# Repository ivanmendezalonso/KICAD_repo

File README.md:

# KICAD_repo
 Aqui estaran todos las carpetas de proyectos

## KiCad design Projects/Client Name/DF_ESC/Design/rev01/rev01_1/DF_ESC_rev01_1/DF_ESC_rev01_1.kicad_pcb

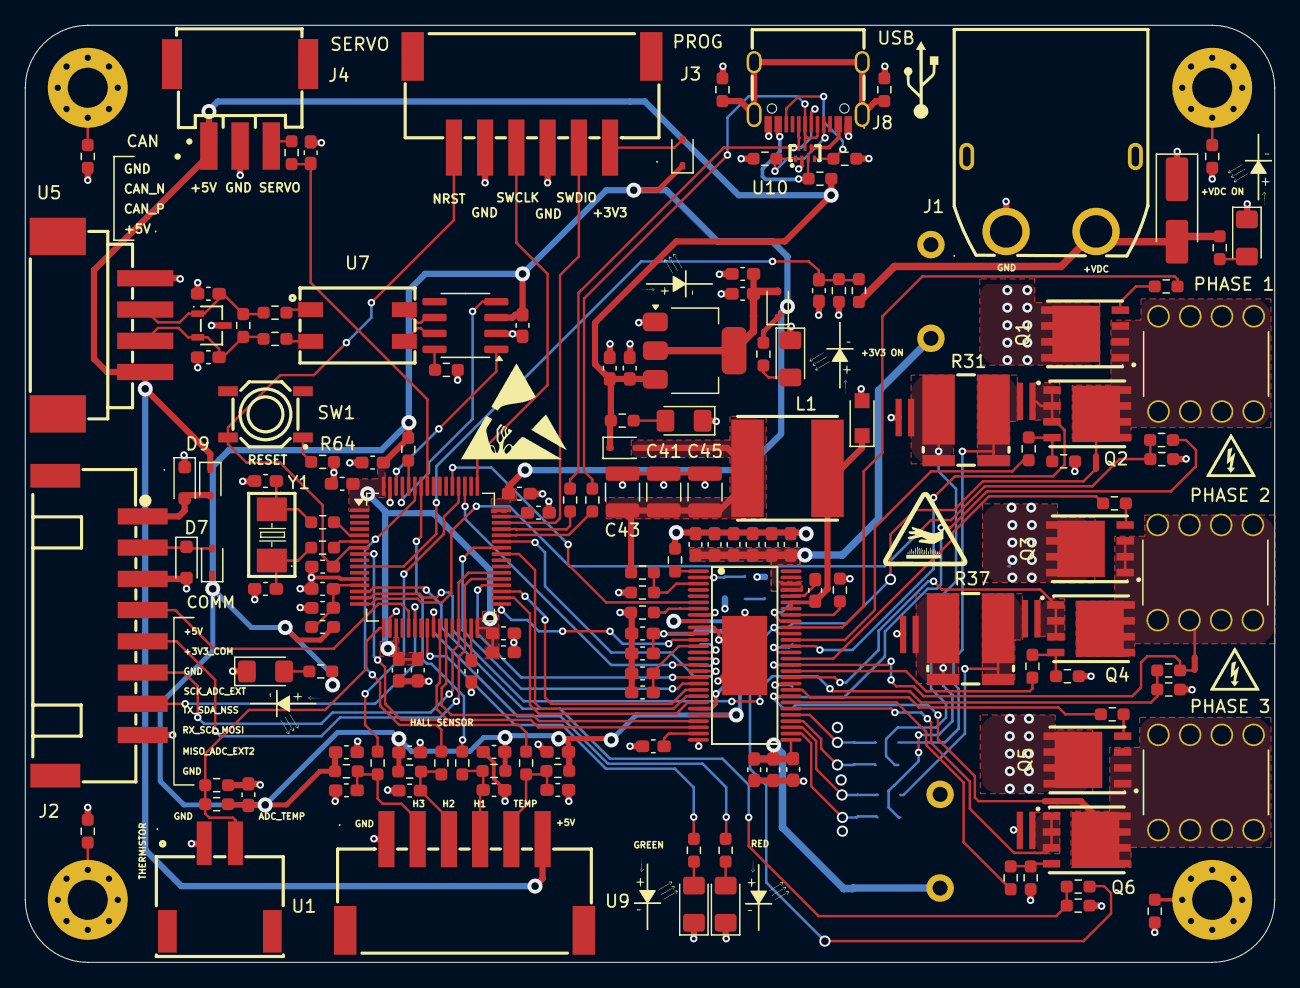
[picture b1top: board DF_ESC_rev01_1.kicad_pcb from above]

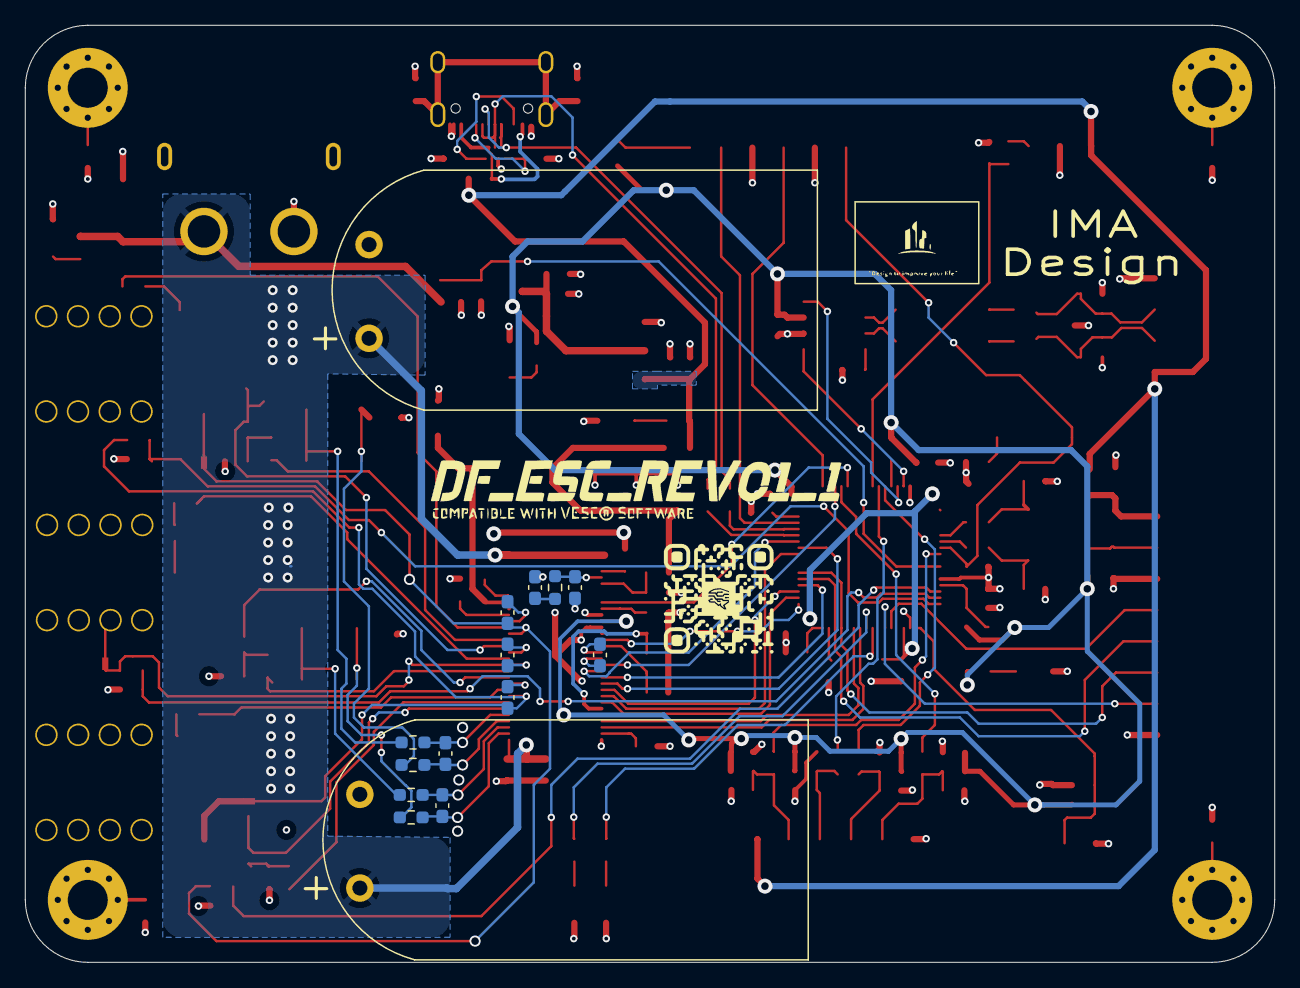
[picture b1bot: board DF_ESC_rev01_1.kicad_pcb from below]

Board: 4 copper layers, 100.0 x 75.0 mm, 183 parts (18 on the bottom side), 125 nets.

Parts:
C1, C2: LKMI2501K821MF; CAP-TH_BD18.0-P7.50-D1.2-SIDE
C3, C4, C10, C11, C12, C15, C16, C17, C19, C21, C23, C32, C33, C34, C35, C39, C42, C46, C57, C58, C59, C60: 100n; C_0603_1608Metric_Pad1.08x0.95mm_HandSolder
C5, C6, C7, C8, C22, C36, C37, C38, C40, C44, C47: 1u; C_0603_1608Metric_Pad1.08x0.95mm_HandSolder
C9: 10u; C_0603_1608Metric_Pad1.08x0.95mm_HandSolder
C13, C14: C; C_0603_1608Metric_Pad1.08x0.95mm_HandSolder
C18, C20, C24, C25, C27, C28, C31: 2u2; C_0603_1608Metric_Pad1.08x0.95mm_HandSolder
C26: 10n; C_0603_1608Metric_Pad1.08x0.95mm_HandSolder
C29: 120p; C_0603_1608Metric_Pad1.08x0.95mm_HandSolder
C30: 22n; C_0603_1608Metric_Pad1.08x0.95mm_HandSolder
C41, C43, C45: 10u; C_1210_3225Metric
C48, C49: 2n2; C_0603_1608Metric_Pad1.08x0.95mm_HandSolder
C50, C51, C52: 51p; C_0603_1608Metric_Pad1.08x0.95mm_HandSolder
C53, C54, C55, C56: 4n7; C_0603_1608Metric_Pad1.08x0.95mm_HandSolder
D1: SMAJ60CA; D_SMA_Handsoldering
D2, D3, D5, D11: LED_G; LED_1206_3216Metric_Pad1.42x1.75mm_HandSolder
D4, D8, D10, D13, D15: BAT60A; D_SOD-323
D6: LED; LED_1206_3216Metric_Pad1.42x1.75mm_HandSolder
D7: PESD3V3U1UA,115; D_SOD-323_HandSoldering
D9: SD05_SOD323; D_SOD-323_HandSoldering
D12: LED_R; LED_1206_3216Metric_Pad1.42x1.75mm_HandSolder
D14: PMEG6020AELR; Nexperia_CFP3_SOD-123W
FB1: FerriteBead; L_0603_1608Metric_Pad1.05x0.95mm_HandSolder
H1, H2, H3, H4: MountingHole_Pad; MountingHole_3.2mm_M3_Pad_Via
J1: XT60PW-M; CONN-TH_XT60PW-M
J2: HX25003-8AWB; CONN-SMD_8P-P2.50_HX25003-8AWB
J3: S6B-XH-SM4-TB(LF)(SN); CONN-SMD_S6B-XH-SM4-TB-LF-SN
J4: XH-3AWB; CONN-SMD_XH-3AWB
J5, J6, J7: 7461084; WE_7461084
J8: USB_C_Receptacle_USB2.0; USB-C_SMD-TYPE-C-31-M-12
L1: 22u; IND-SMD_L7.8-W7.8_SDR0805
LOGO1: DF_LOGO; DF_ESC_REV01_1_LOGO
LOGO2: DF_LOGO_NO_SLK
NT1, NT4, NT7: NetTie_2; NetTie-2_SMD_Pad0.5mm
NT2, NT3, NT5, NT6, NT8: Net_Tie_PWR; NetTie_SMD_Pad_3.00mm
Q1, Q2, Q3, Q4, Q5, Q6: HSBA15810C; PQFN-8_L6.0-W5.0-P1.27-LS6.0-BL
QR1: DF_QR_CODE
R1, R3, R13, R21, R23, R25, R45, R46, R47, R48, R64: 2k2; R_0603_1608Metric_Pad0.98x0.95mm_HandSolder
R2, R4, R30, R36, R40: 39k; R_0603_1608Metric_Pad0.98x0.95mm_HandSolder
R5, R6, R7, R10, R11: 1k; R_0603_1608Metric_Pad0.98x0.95mm_HandSolder
R8, R9: R; R_0603_1608Metric_Pad0.98x0.95mm_HandSolder
R12, R53, R54, R55, R60, R61, R62, R63: 0R; R_0603_1608Metric_Pad0.98x0.95mm_HandSolder
R14: 16k; R_0603_1608Metric_Pad0.98x0.95mm_HandSolder
R15, R49, R50, R51, R52: 10k; R_0603_1608Metric_Pad0.98x0.95mm_HandSolder
R16: 205k; R_0603_1608Metric_Pad0.98x0.95mm_HandSolder
R17: 1M; R_0603_1608Metric_Pad0.98x0.95mm_HandSolder
R18, R20, R22, R24: 18k; R_0603_1608Metric_Pad0.98x0.95mm_HandSolder
R19: 3k3; R_0603_1608Metric_Pad0.98x0.95mm_HandSolder
R26, R27, R32, R33, R38, R39: 4R7; R_0603_1608Metric_Pad0.98x0.95mm_HandSolder
R28, R29, R34, R35: 100R; R_0603_1608Metric_Pad0.98x0.95mm_HandSolder
R31, R37: 0R001; RES-SMD_L7.0-W6.7
R41: 120R; R_0603_1608Metric_Pad0.98x0.95mm_HandSolder
R42, R43, R44: 10R; R_0603_1608Metric_Pad0.98x0.95mm_HandSolder
R56, R57: 5k1; R_0603_1608Metric_Pad0.98x0.95mm_HandSolder
R58, R59: 22R; R_0603_1608Metric_Pad0.98x0.95mm_HandSolder
SW1: SW_DIP_x01; SW-SMD_4P-L5.2-W5.2-P3.70-LS6.4
TH1: Thermistor_NTC; R_0603_1608Metric_Pad0.98x0.95mm_HandSolder
U1: XH-2PWBPZ; CONN-SMD_XH-2PWBPZ
U2: AMS1117-3.3; SOT-223-3_TabPin2
U3: STM32F405RGTx; LQFP-64_10x10mm_P0.5mm
U4: DRV8302DCAR; HTSSOP-56_L14.0-W6.1-P0.50-LS8.1-BL-EP
U5: S4B-XH-SM4-TB-(LF)(SN); CONN-SMD_S4B-XH-SM4-TB-LF-SN
U6: ESDCAN24-2BLY; SOT-23-3_L3.0-W1.7-P0.95-LS2.9-BR
U7: 744227S; FILTER-SMD_4P-L9.2-W6.0-P2.54-TL
U8: SN65HVD230; SOIC-8_3.9x4.9mm_P1.27mm
U9: S6B-XH-SM4-TB(LF)(SN); CONN-SMD_S6B-XH-SM4-TB-LF-SN
U10: PUSB3AB6Z; XSON-7_L2.2-W1.2-P0.50-BL
Y1: Crystal_Small; CRYSTAL-SMD_L5.0-W3.2

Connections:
+3V3: C3.1, C9.1, C10.1, C11.1, C12.1, C15.1, C16.1, C17.1, C52.1, C57.1, C58.1, C59.1, C60.1, D4.1 (K), D8.1 (K), D13.1 (K), FB1.2, R1.1, R6.1, R7.1, R12.1, R45.1, R46.1, R47.1, R48.1, U3.1 (VBAT), U3.19 (VDD), U3.32 (VDD), U3.48 (VDD), U3.64 (VDD), U4.9 (M_OC), U4.24 (REF), U8.3 (VCC)
+5V: C5.1, C6.1, D10.1 (K), D15.1 (K), J4.1, R5.1, R55.1, U2.3 (VI), U5.4, U9.6
+VDC: C1.1, C2.1, C32.2, C33.2, C35.2, C36.1, C37.1, C38.1, C40.1, C44.1, C47.1, D1.2 (A2), J1.2 (+), Q1.5 (D), Q1.6 (D), Q1.7 (D), Q1.8 (D), Q1.9 (D), Q3.5 (D), Q3.6 (D), Q3.7 (D), Q3.8 (D), Q3.9 (D), Q5.5 (D), Q5.6 (D), Q5.7 (D), Q5.8 (D), Q5.9 (D), R2.1, R4.1, U4.29 (PVDD1), U4.53 (PVDD2), U4.54 (PVDD2)
/[3] - STEP DOWN/+3V3_IC: C7.1, C8.1, D4.2 (A), U2.2 (VO)
/[4] - MCU/+3V3_COM: D7.1, D8.2 (A), J2.2
/[4] - MCU/+5V_COM: D9.2 (A2), D10.2 (A), J2.1
/[4] - MCU/BOOT0_P: R12.2, U3.60 (BOOT0)
/[4] - MCU/LED_GREEN: R10.1, U3.24 (PC4)
/[4] - MCU/LED_RED: R11.1, U3.25 (PC5)
/[4] - MCU/MISO_ADC_EXT2: J2.7, U3.22 (PA6)
/[4] - MCU/NRST: C19.1, J3.6, SW1.2, U3.7 (NRST)
/[4] - MCU/PH_0: C13.2, R8.1, Y1.2
/[4] - MCU/PH_0_P: R8.2, U3.5 (PH0)
/[4] - MCU/PH_1: C14.2, R9.1, Y1.1
/[4] - MCU/PH_1_P: R9.2, U3.6 (PH1)
/[4] - MCU/RX_SCL_MOSI: J2.6, U3.29 (PB10), U3.38 (PC7)
/[4] - MCU/SCK_ADC_EXT: J2.4, U3.21 (PA5)
/[4] - MCU/SERVO: C23.1, R13.1, U3.57 (PB5)
/[4] - MCU/SWCLK: J3.4, U3.49 (PA14)
/[4] - MCU/SWDIO: J3.2, U3.46 (PA13)
/[4] - MCU/TX_SDA_NSS: J2.5, U3.30 (PB11), U3.37 (PC6)
/[4] - MCU/VCAP_1: C18.1, U3.31 (VCAP_1)
/[4] - MCU/VCAP_2: C20.1, U3.47 (VCAP_2)
/[5] - MOSFET DRIVER/+5V_DRV: C41.1, C43.1, C45.1, D15.2 (A), L1.2, R18.1
/[5] - MOSFET DRIVER/BIAS: R17.1, U4.49 (BIAS)
/[5] - MOSFET DRIVER/BST_A: C39.2, U4.48 (BST_A)
/[5] - MOSFET DRIVER/BST_B: C42.2, U4.43 (BST_B)
/[5] - MOSFET DRIVER/BST_BK: C34.1, U4.52 (BST_BK)
/[5] - MOSFET DRIVER/BST_C: C46.2, U4.38 (BST_C)
/[5] - MOSFET DRIVER/COMP: C29.2, R14.2, U4.2 (COMP)
/[5] - MOSFET DRIVER/CP1: C30.2, U4.14 (CP1)
/[5] - MOSFET DRIVER/CP2: C30.1, U4.15 (CP2)
/[5] - MOSFET DRIVER/DTC: R15.2, U4.7 (DTC)
/[5] - MOSFET DRIVER/DVDD: C24.1, C27.1, U4.11 (OC_ADJ), U4.23 (DVDD)
/[5] - MOSFET DRIVER/GVDD: C25.1, C28.1, U4.13 (GVDD)
/[5] - MOSFET DRIVER/PH: C34.2, D14.1 (K), L1.1, U4.50 (PH), U4.51 (PH)
/[5] - MOSFET DRIVER/RT_CLK: R16.2, U4.1 (RT_CLK)
/[5] - MOSFET DRIVER/VSENSE: R18.2, R19.1, U4.3 (VSENSE)
/[6] - MOSFETs/M_H1_RG: Q1.4 (G), R27.2
/[6] - MOSFETs/M_H2_RG: Q3.4 (G), R33.2
/[6] - MOSFETs/M_H3_RG: Q5.4 (G), R39.2
/[6] - MOSFETs/M_L1_RG: Q2.4 (G), R26.2, R30.2
/[6] - MOSFETs/M_L2_RG: Q4.4 (G), R32.2, R36.2
/[6] - MOSFETs/PHASE_1: J5.1, J5.2 (1), J5.3 (1), J5.4 (1), J5.5 (1), J5.6 (1), J5.7 (1), J5.8 (1), NT1.1, Q1.1 (S), Q1.2 (S), Q1.3 (S), Q2.5 (D), Q2.6 (D), Q2.7 (D), Q2.8 (D), Q2.9 (D)
/[6] - MOSFETs/PHASE_2: J6.1, J6.2 (1), J6.3 (1), J6.4 (1), J6.5 (1), J6.6 (1), J6.7 (1), J6.8 (1), NT4.1, Q3.1 (S), Q3.2 (S), Q3.3 (S), Q4.5 (D), Q4.6 (D), Q4.7 (D), Q4.8 (D), Q4.9 (D)
/[6] - MOSFETs/PHASE_3: J7.1, J7.2 (1), J7.3 (1), J7.4 (1), J7.5 (1), J7.6 (1), J7.7 (1), J7.8 (1), NT7.1, Q5.1 (S), Q5.2 (S), Q5.3 (S), Q6.5 (D), Q6.6 (D), Q6.7 (D), Q6.8 (D), Q6.9 (D)
/[6] - MOSFETs/SH1_N: NT6.1, R28.2, R31.2
/[6] - MOSFETs/SH1_P: NT8.2, R29.2, R31.1
/[6] - MOSFETs/SH2_N: NT3.1, R34.2, R37.2
/[6] - MOSFETs/SH2_P: NT5.2, R35.2, R37.1
/[7] - CAN/CAN_N: U7.4, U8.6 (CANL)
/[7] - CAN/CAN_P: U7.3, U8.7 (CANH)
/[7] - CAN/C_CAN_N: C51.1, R41.2, R43.1, U5.2, U6.1
/[7] - CAN/C_CAN_P: C50.2, R41.1, R42.1, U5.3, U6.2
/[7] - CAN/R_CAN_N: R43.2, U7.1
/[7] - CAN/R_CAN_P: R42.2, U7.2
/[8] - FILTERS/HALL_1_IN: C53.1, R45.2, R49.1, U9.4
/[8] - FILTERS/HALL_2_IN: C54.1, R46.2, R50.1, U9.3
/[8] - FILTERS/HALL_3_IN: C55.1, R47.2, R51.1, U9.2
/[8] - FILTERS/TEMP_IN: C56.1, R48.2, R52.1, U9.5
/[9] - USB/+5V_C: J8.A4 (VBUS), J8.A9 (VBUS), J8.B4 (VBUS), J8.B9 (VBUS), R55.2, U10.3 (CH2), U10.5 (CH4)
/[9] - USB/CC1: J8.A5 (CC1), R57.1, U10.1 (CH1)
/[9] - USB/CC2: J8.B5 (CC2), R56.1, U10.4 (CH3)
/[9] - USB/USB-C_N: J8.A7 (D-), J8.B7 (D-), R58.1, U10.6 (CH5)
/[9] - USB/USB-C_P: J8.A6 (D+), J8.B6 (D+), R59.1, U10.7 (CH6)
ADC_TEMP: R1.2, TH1.1, U1.2, U3.17 (PA3)
AN_IN: C4.1, R2.2, R3.1, U3.10 (PC2)
BR_S01: U3.27 (PB1), U4.25 (SO1)
BR_S02: U3.26 (PB0), U4.26 (SO2)
CAN_RX: U3.61 (PB8), U8.4 (R)
CAN_TX: U3.62 (PB9), U8.1 (D)
DC_CAL: U3.33 (PB12), U4.12 (DC_CAL)
EN_GATE: U3.51 (PC10), U4.16 (EN_GATE)
FAULT: U3.53 (PC12), U4.6 (nFAULT)
GND: C1.2, C2.2, C3.2, C4.2, C5.2, C6.2, C7.2, C8.2, C9.2, C10.2, C11.2, C12.2, C13.1, C14.1, C15.2, C16.2, C17.2, C18.2, C19.2, C20.2, C21.2, C22.2, C23.2, C24.2, C25.2, C26.1, C27.2, C28.2, C29.1, C31.2, C32.1, C33.1, C35.1, C36.2, C37.2, C38.2, C40.2, C41.2, C43.2, C44.2, C45.2, C47.2, C50.1, C51.2, C52.2, C53.2, C54.2, C55.2, C56.2, C57.2, C58.2, C59.2, C60.2, D1.1 (A1), D2.1 (K), D3.1 (K), D5.1 (K), D6.1 (K), D7.2, D9.1 (A1), D11.1 (K), D12.1 (K), D14.2 (A), J1.1 (-), J2.3, J2.8, J3.3, J3.5, J4.2, J8.A1 (GND), J8.A12 (GND), J8.B1 (GND), J8.B12 (GND), NT2.1, NT5.1, NT8.1, R3.2, R15.1, R16.1, R17.2, R19.2, R21.2, R23.2, R25.2, R30.1, R36.1, R40.1, R44.1, R53.2, R54.2, R56.2, R57.2, R60.2, R61.2, R62.2, R63.2, R64.2, TH1.2, U1.1, U2.1 (GND), U3.12 (VSSA), U3.18 (VSS), U3.63 (VSS), U4.8 (M_PWM), U4.10 (GAIN), U4.28 (AGND), U4.57 (GND), U5.1, U6.3, U8.2 (GND), U9.1, U10.2 (GND)
H1: U3.43 (PA10), U4.17 (INH_A)
H1_LOW: NT6.2, Q2.1 (S), Q2.2 (S), Q2.3 (S), U4.44 (SL_A)
H1_VS: C39.1, NT1.2, R24.1, U4.46 (SH_A)
H2: U3.42 (PA9), U4.19 (INH_B)
H2_LOW: NT3.2, Q4.1 (S), Q4.2 (S), Q4.3 (S), U4.39 (SL_B)
H2_VS: C42.1, NT4.2, R22.1, U4.41 (SH_B)
H3: U3.41 (PA8), U4.21 (INH_C)
H3_LOW: NT2.2, Q6.1 (S), Q6.2 (S), Q6.3 (S), U4.34 (SL_C)
H3_VS: C46.1, NT7.2, R20.1, U4.36 (SH_C)
HALL_1_OUT: R49.2, U3.58 (PB6)
HALL_2_OUT: R50.2, U3.59 (PB7)
HALL_3_OUT: R51.2, U3.52 (PC11)
L1: U3.36 (PB15), U4.18 (INL_A)
L2: U3.35 (PB14), U4.20 (INL_B)
L3: U3.34 (PB13), U4.22 (INL_C)
M_H1: R27.1, U4.47 (GH_A)
M_H2: R33.1, U4.42 (GH_B)
M_H3: R39.1, U4.37 (GH_C)
M_L1: R26.1, U4.45 (GL_A)
M_L2: R32.1, U4.40 (GL_B)
M_L3: R38.1, U4.35 (GL_C)
unnamed: C26.2, R14.1
unnamed: D2.2 (A), R4.2
unnamed: D3.2 (A), R5.2
unnamed: D5.2 (A), R6.2
unnamed: D6.2 (A), R7.2
unnamed: D11.2 (A), R10.2
unnamed: D12.2 (A), R11.2
unnamed: D13.2 (A), J3.1
unnamed: H1.1, R60.1
unnamed: H2.1, R61.1
unnamed: H3.1, R62.1
unnamed: H4.1, R63.1
unnamed: J4.3, R13.2
unnamed: J8.S1 (SHIELD), J8.S2 (SHIELD), R53.1, R54.1
unnamed: Q6.4 (G), R38.2, R40.2
unnamed: R64.1, SW1.1
unnamed: C21.1, C22.1, FB1.1, U3.13 (VDDA)
unnamed: C31.1, U4.27 (AVDD)
unnamed: R44.2, U8.8 (Rs)
S1_N: C48.1, R28.1, U4.33 (SN1)
S1_P: C48.2, R29.1, U4.32 (SP1)
S2_N: C49.1, R34.1, U4.31 (SN2)
S2_P: C49.2, R35.1, U4.30 (SP2)
SENS1: R20.2, R21.1, U3.16 (PA2)
SENS2: R22.2, R23.1, U3.15 (PA1)
SENS3: R24.2, R25.1, U3.14 (PA0)
TEMP_MOTOR: R52.2, U3.8 (PC0)
USB_N: R58.2, U3.44 (PA11)
USB_P: R59.2, U3.45 (PA12)

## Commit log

2024-01-10 update_10-01-2024
    copiar folder estrcture de ejemplo y subirlo desde casa
2024-01-12 Update_12-01-2024-1
    Cambios de la realizacion de la lesson 3. Faltan ultimos 5 min
2024-01-13 Update 13-01-2024
    Terminar de crear templates para schematics y PCB. Example project
2024-01-14 Update 14-01-2023
    Block diagram
2024-01-18 Update 18-01-2024
    MCU - Decoupling capacitor zone
2024-01-19 Update 19-01-2024 primera
    cambiar y añadir numeracion de sheets
2024-01-19 Update 19-01-2024_2
2024-01-19 Update 19-01-2024_3
    MCU schematic complete
2024-01-22 Update 22-01-2023_1
    DRV8302 Symbol
2024-01-23 Udpate 23-01-2024_Prueba
    Solo se borro para probar cambio de carpeta KICAD_directorio por Github
2024-01-23 update 23-01-2024_prueba2
    revirtiendo lo hecho
2024-01-23 Update 23-01-2024_prueba3
2024-01-23 Update 23-01-2024_4
    Volver la situacion de origen antes de las pruebas
2024-01-23 Update 23-01-2024_prueba 5
    Quitar la U de MCU para probar
2024-01-25 update 25-01-2024
2024-01-25 update 25-01-2024_2
2024-01-28 Update 28-01-2024
    MOSFET_DRIVER casi completo
2024-01-30 Update 30-01-2024
    Schematico motor driver terminado
2024-01-30 Update 30-01-2024
    instalacion pip install JLC2KiCadLib
2024-01-30 update 31-01-2024
    BorrarJLC2KICAD_lib-master
2024-01-31 Update 31-01-2024
    Ahora sí que he cargado el pip y JLC2KiCadLib C1337258
2024-01-31 31-01-2024-4
2024-01-31 Update 31-01-2024
    Prueba bajar componente 1
2024-01-31 Update 31-01-2024 final DRV8302
2024-02-12 Update 12-02-2024_1
    Empiece schematic mosfet
2024-02-13 update 12-02-2024
2024-02-24 home Santander 24-02-2024
    Acabados los mosfets
2024-02-27 update 2024-02-27
2024-02-28 Update 2024-02-28_2
    Input Proteccion Done
2024-02-29 update 2024-02-29
    CAN Page DONE
2024-03-02 Update 2024-02-03
    Schematic finish but DRC CHEK Errors
2024-03-03 Update 2024-03-03
    ERC 0 Errors. Update PCB from schematics prepare to going on
2024-03-03 Update 2024-03-03_2
2024-03-04 Update 2024-03-04_3
    Cambiado y ajustado a rejilla 1.27 mm
2024-03-04 update final 2024-03-04
2024-03-11 update 2024-03-11
2024-03-12 update 2024-03-12_1
2024-03-13 update 2024-03-13
    Listo para pasar a PCB
2024-03-13 Update 2024-03-13_2
    Version final para posicionar PCB
2024-03-17 update 17-03-2024_1
2024-03-17 update 17-03-2024_2
2024-03-28 update 2024-03-28
    lesson 13 fineshed
2024-04-07 update 07-04-2024
2024-04-16 Update 20240416
    Lesson 16 finished
2024-04-18 update 2024-04-18
2024-04-19 update 20240419
    preliminari Routing
2024-04-21 update 20240421
2024-04-22 Update DF_ESC_rev01_1.kicad_pcb
    Layout preliminar finished
2024-04-23 update 20240423
2024-04-23 update 20240423_2
    Layout rehecho y terminado en casa falta solo mejorarlo
2024-04-24 update 20240424
    Layout mejorado y terminado. Dar un ultimo repaso
2024-04-24 update 20240424_2
    Ultimos detalles desde casa
2024-04-25 update 20240425_casa
2024-04-27 update 20240427
    Mejora de layout cero errores, solo falta añadir algunas reseñas en el silkscreen
2024-04-28 update 20240428
2024-04-28 update 20240428_2
2024-05-09 update 09-05-2024
2024-05-09 update 20240509_2
2024-05-11 Update 20240511
    Serigrafia de fabricacion completa
2024-05-11 update 20240512
    gerbers generated
2024-05-12 Update DF_ESC_rev01_1.kicad_pcb
    Proyecto finalizado
